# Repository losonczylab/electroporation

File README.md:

# electroporation
Repository for electronics and hardware design files for the single-cell electroporation rig.

Publication Link:
https://pubmed.ncbi.nlm.nih.gov/39930062/

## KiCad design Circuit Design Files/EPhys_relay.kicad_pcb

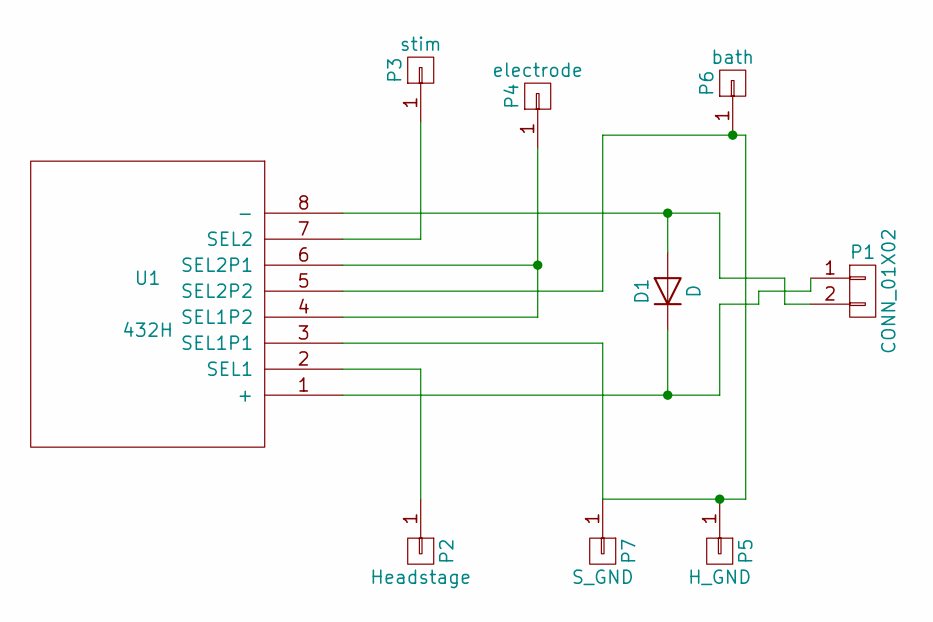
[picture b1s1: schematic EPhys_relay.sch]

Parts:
D1: D; D_SOD-123
P1: CONN_01X02; Connectors_JST_S2B-PH-K
P2: Headstage; PINTST
P3: stim; PINTST
P4: electrode; PINTST
P5: H_GND; PINTST
P6: bath; PINTST
P7: S_GND; PINTST
U1: 432H; TO-5-8

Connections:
unnamed: D1.1 (K), P1.1, U1.1 (+)
unnamed: D1.2 (A), P1.2, U1.8 (-)
unnamed: P2.1, U1.2 (SEL1)
unnamed: P3.1, U1.7 (SEL2)
unnamed: P4.1, U1.4 (SEL1P2), U1.6 (SEL2P1)
unnamed: P5.1, P6.1, P7.1, U1.3 (SEL1P1), U1.5 (SEL2P2)

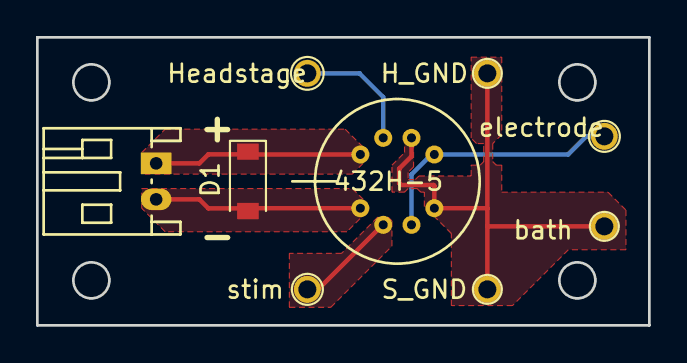
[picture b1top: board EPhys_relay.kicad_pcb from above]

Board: 2 copper layers, 34.0 x 16.0 mm, 9 parts (0 on the bottom side), 6 nets.

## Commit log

2024-01-18 readme
2024-01-18 hardware and electronics design files
2024-03-08 file organization. Added images
2024-03-08 removed bill of material since all the links are already in the paper
2024-03-08 removed images since they are all in the paper
2024-04-11 Added cannula file
2024-07-01 Create head post
2024-07-01 SCE cannula
2024-07-01 Surgery
2024-07-01 sce circuit
